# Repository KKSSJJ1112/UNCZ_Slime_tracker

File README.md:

<h2 align="center">🚧 開発中 / 개발중 / Under Development 🚧</h2>

---

# UNCZ SlimeVR Tracker

[🇯🇵 日本語](#日本語) | [🇰🇷 한국어](#한국어) | [🇺🇸 English](#english)

<p align="center">
  <!-- 実演GIF / 실연 GIF / Demo GIF -->
  
</p>

---

## 日本語

### 1. 概要

UNCZ SlimeVR Tracker は SlimeVR エコシステム互換のカスタム IMU トラッカーボードである。ESP32-C3 を中心に IMU・磁気センサ・バッテリー充電・昇降圧 DC-DC を 1 枚に統合し、USB-C 1 ポートで充電とファームウェア書き込みを兼ねる構成となっている。

- ボードサイズ: **約 50mm × 35mm**
- 電源: 1 セル Li-ion / Li-Po **1100mAh**
- 通信: Wi-Fi (ESP32-C3 内蔵)
- 充電/通信: USB-C 単一ポート
- 4 層 PCB 設計

### 2. 使用 IC 一覧

| 役割 | 型番 | 主な仕様 |
|------|------|----------|
| MCU | ESP32-C3-MINI-1-H4X | RISC-V, Wi-Fi/BLE, 内蔵アンテナ |
| 昇降圧 DC-DC | TPS63802DSGR | Iq 11µA, EN ピン制御 |
| 充電 IC | BQ24232HRGTR | パワーパス内蔵, OVP 28V |
| IMU | LSM6DSV16XTR | 6 軸, I²C 0x6B |
| 磁気センサ | QMC6309 | 3 軸, I²C 0x7C (オプション実装) |
| USB データ TVS | USBLC6-2SC6 | D+/D- ESD 保護 |
| バッテリー | 1100mAh 1S Li-ion/Li-Po | 公称 3.7V |

### 3. 出力 CLC フィルタ

TPS63802 の出力リップル抑制のため、共振周波数 **約 1.4MHz** をターゲットとした CLC フィルタを実装している。

**フィルタ構成**
- C1 (前段): **10µF**
- L: **1µH**
- C2 (後段): **10µF**
- 共振周波数: f₀ = 1 / (2π√(LC)) ≈ 1.59MHz (C 並列換算)

**スナバ・ダンピング**
LC 共振による Q 値スパイクを抑えるため、後段に並列スナバを配置。
- ダンピング抵抗: **1Ω 抵抗 × 3 個並列 = 0.33Ω**
- スナバ容量: **22µF × 3 個並列 = 66µF**

この構成によりフィルタの Q 値を適切に下げ、過渡応答時のリンギングを抑制している。

<p align="center">
  <!-- LTspice シミュレーション画像 -->
  
</p>

### 4. ファイル構成

| フォルダ | 内容 |
|----------|------|
| `pic/` | 測定写真、実演 GIF |
| `EASY_EDA_PRO/` | EasyEDA Pro プロジェクトファイル、ライブラリファイル |
| `JLC_PCB/` | ガーバーファイル、BOM、Pick & Place ファイル |
| `Datasheet/` | 使用部品のデータシート |
| `Firmware/` | SlimeVR オープンソースベースのファームウェア |
| `License/` | ライセンスファイル |

### 5. ファームウェア

本プロジェクトのファームウェアに関するすべての部分は **[SlimeVR オープンソースプロジェクト](https://github.com/SlimeVR/SlimeVR-Tracker-ESP)** に準拠する。

### 6. リビジョン履歴

| Rev | 内容 |
|-----|------|
| REV1 | モジュールベースの拡張ボード設計 |
| REV5 | チップベースの再設計 (現行) |

### 7. ライセンス

- **ハードウェア (PCB, 回路図, 3D ファイル)**: [MIT License](https://github.com/KKSSJJ1112/UNCZ_Slime_tracker/blob/main/License/MIT)
- **ドキュメント**: [CC BY-SA 4.0](https://creativecommons.org/licenses/by-sa/4.0/)

---

## 한국어

### 1. 개요

UNCZ SlimeVR Tracker는 SlimeVR 생태계와 호환되는 커스텀 IMU 트래커 보드입니다. ESP32-C3를 중심으로 IMU, 자력계, 배터리 충전 회로, 벅부스트 DC-DC를 한 장의 PCB에 통합했으며, 단일 USB-C 포트로 충전과 펌웨어 장입을 모두 처리합니다.

- 보드 사이즈: **약 50mm × 35mm**
- 전원: 1셀 Li-ion / Li-Po **1100mAh**
- 통신: Wi-Fi (ESP32-C3 내장)
- 충전/통신: USB-C 단일 포트
- 4레이어 PCB 설계

### 2. 사용 IC 목록

| 역할 | 부품 | 주요 사양 |
|------|------|-----------|
| MCU | ESP32-C3-MINI-1-H4X | RISC-V, Wi-Fi/BLE, 내장 안테나 |
| 벅부스트 DC-DC | TPS63802DSGR | Iq 11µA, EN 핀 제어 |
| 충전 IC | BQ24232HRGTR | 파워패스 내장, OVP 28V |
| IMU | LSM6DSV16XTR | 6축, I²C 0x6B |
| 자력계 | QMC6309 | 3축, I²C 0x7C (옵션 실장) |
| USB 데이터 TVS | USBLC6-2SC6 | D+/D- ESD 보호 |
| 배터리 | 1100mAh 1S Li-ion/Li-Po | 공칭 3.7V |

### 3. 출력 CLC 필터

TPS63802 출력 리플 억제를 위해 공진 주파수 **약 1.4MHz**를 타겟으로 한 CLC 필터를 구성했습니다.

**필터 구성**
- C1 (전단): **10µF**
- L: **1µH**
- C2 (후단): **10µF**
- 공진 주파수: f₀ = 1 / (2π√(LC)) ≈ 1.59MHz (C 병렬 환산)

**스너버 댐핑**
LC 공진으로 인한 Q값 스파이크를 억제하기 위해 후단에 병렬 스너버를 배치하여 의도적으로 Q값을 조정했습니다.
- 댐핑 저항: **1Ω 저항 3개 병렬 = 0.33Ω**
- 스너버 커패시터: **22µF 3개 병렬 = 66µF**

이 구성으로 필터의 Q값을 적절히 낮춰 과도 응답 시 링잉을 억제합니다.

<p align="center">
  <!-- LTspice 시뮬레이션 이미지 -->
  
</p>

### 4. 파일 구성

| 폴더 | 내용 |
|------|------|
| `pic/` | 측정 사진, 실연 GIF |
| `EASY_EDA_PRO/` | EasyEDA Pro 프로젝트 파일, 라이브러리 파일 |
| `JLC_PCB/` | 거버 파일, BOM, Pick & Place 파일 |
| `Datasheet/` | 사용 부품 데이터시트 |
| `Firmware/` | SlimeVR 오픈소스 기반 펌웨어 |
| `License/` | 라이센스 파일 |

### 5. 펌웨어

본 프로젝트의 펌웨어와 관련된 모든 부분은 **[SlimeVR 오픈소스 프로젝트](https://github.com/SlimeVR/SlimeVR-Tracker-ESP)** 를 따릅니다.

### 6. 리비전 히스토리

| Rev | 내용 |
|-----|------|
| REV1 | 모듈 기반의 확장 보드 설계 |
| REV5 | 칩 기반의 재설계 (현행) |

### 7. 라이센스

- **하드웨어 (PCB, 회로도, 3D 파일)**: [MIT License](https://github.com/KKSSJJ1112/UNCZ_Slime_tracker/blob/main/License/MIT)
- **문서**: [CC BY-SA 4.0](https://creativecommons.org/licenses/by-sa/4.0/)

---

## English

### 1. Overview

The UNCZ SlimeVR Tracker is a custom IMU tracker board compatible with the SlimeVR ecosystem. Built around the ESP32-C3, it integrates an IMU, magnetometer, battery charger, and buck-boost DC-DC converter onto a single PCB, with a single USB-C port handling both charging and firmware upload.

- Board size: **~50mm × 35mm**
- Power: 1-cell Li-ion / Li-Po **1100mAh**
- Communication: Wi-Fi (ESP32-C3 built-in)
- Charging/Communication: Single USB-C port
- 4-layer PCB design

### 2. IC List

| Role | Part | Key Specs |
|------|------|-----------|
| MCU | ESP32-C3-MINI-1-H4X | RISC-V, Wi-Fi/BLE, built-in antenna |
| Buck-Boost DC-DC | TPS63802DSGR | Iq 11µA, EN pin control |
| Charger IC | BQ24232HRGTR | Power path built-in, OVP 28V |
| IMU | LSM6DSV16XTR | 6-axis, I²C 0x6B |
| Magnetometer | QMC6309 | 3-axis, I²C 0x7C (optional) |
| USB Data TVS | USBLC6-2SC6 | D+/D- ESD protection |
| Battery | 1100mAh 1S Li-ion/Li-Po | Nominal 3.7V |

### 3. Output CLC Filter

A CLC filter targeting a resonant frequency of **~1.4MHz** is implemented to suppress output ripple from the TPS63802.

**Filter Configuration**
- C1 (front): **10µF**
- L: **1µH**
- C2 (rear): **10µF**
- Resonant frequency: f₀ = 1 / (2π√(LC)) ≈ 1.59MHz (with parallel C)

**Snubber Damping**
To suppress the Q-factor spike caused by LC resonance, a parallel snubber is placed at the rear stage, intentionally tuning the Q-factor.
- Damping resistor: **1Ω × 3 in parallel = 0.33Ω**
- Snubber capacitor: **22µF × 3 in parallel = 66µF**

This configuration appropriately lowers the filter's Q-factor, suppressing ringing during transient response.

<p align="center">
  <!-- LTspice simulation image -->
  
</p>

### 4. File Structure

| Folder | Contents |
|--------|----------|
| `pic/` | Measurement photos, demo GIFs |
| `EASY_EDA_PRO/` | EasyEDA Pro project files, library files |
| `JLC_PCB/` | Gerber files, BOM, Pick & Place files |
| `Datasheet/` | Datasheets of used components |
| `Firmware/` | SlimeVR open-source-based firmware |
| `License/` | License files |

### 5. Firmware

All firmware-related portions of this project follow the **[SlimeVR open-source project](https://github.com/SlimeVR/SlimeVR-Tracker-ESP)**.

### 6. Revision History

| Rev | Description |
|-----|-------------|
| REV1 | Module-based expansion board design |
| REV5 | Chip-based redesign (current) |

### 7. License

- **Hardware (PCB, Schematics, 3D files)**: [MIT License](https://github.com/KKSSJJ1112/UNCZ_Slime_tracker/blob/main/License/MIT)
- **Documentation**: [CC BY-SA 4.0](https://creativecommons.org/licenses/by-sa/4.0/)

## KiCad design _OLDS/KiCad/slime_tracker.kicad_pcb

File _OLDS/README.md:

# UNCZ_Slime_tracker

[English](#english) | [한국어](#한국어)

---

## English

### Overview
Custom SlimeVR tracker.

### Specifications
| Item | Description |
|------|-------------|
| MCU | ESP32-C3 Super Mini |
| IMU | SlimeVR Mumo Breakout Module V1 (ICM-45686 + QMC6309) |
| Battery | 1100mAh Li-Po |
| PCB Size | ~80mm x 30mm |

## REV01
<details>
### Features
- **Optimized Power Circuit**: Minimized ripple and noise (77mV → 20mV)
- **Compact Form Factor**: Streamlined 2-layer PCB design
- **Production Ready**: Includes JLCPCB manufacturing files

### Repository Structure
```
├── 3D/                    # 3D model files (STL - case, mount, etc.)
├── Datasheets/            # Component datasheets
├── Demonstration_Video/   # Demo videos
├── SlimeVR/               # SlimeVR firmware source code
├── KiCad/                 # KiCad project files
│   ├── *.kicad_pcb
│   ├── *.kicad_sch
│   └── *.kicad_pro
├── License/               # License files
├── Measurement_Pic/       # Power circuit ripple measurement photos
└── Production/            # Manufacturing files
    ├── BOM.csv            # Bill of Materials (JLCPCB format)
    └── Positions.csv      # Pick and place file
```

### Manufacturing
Production files are optimized for JLCPCB:
1. Generate Gerber and drill files from KiCad project (`KiCad/` folder)
2. Upload generated Gerber files to JLCPCB
3. Use provided BOM and position files for SMT assembly

### Firmware

Based on the official SlimeVR open-source firmware.  
Original repository: https://github.com/SlimeVR/SlimeVR-Tracker-ESP

This repository contains only the modified files. Clone the original repository first, then apply these changes.

#### Modified Files

| File | Changes |
|------|---------|
| `src/defines.h` | Hardcoded WiFi credentials, battery monitoring disabled, dual sensor config (`SENSOR_DESC_LIST` - 0x69, 0x68), SDO pin control (`PIN_IMU_SDO = 5`) |
| `src/main.cpp` | SDO pin initialization (GPIO5 → HIGH, 200ms delay), WiFi credentials fallback |
| `src/network/wifihandler.cpp` | Hardcoded WiFi credentials (`tryHardcodedCredentials()` function) |
| `src/network/wifihandler.h` | WiFi timeout reduced: 11s → 4s |
| `src/sensors/softfusion/drivers/icm45base.h` | Default I2C address changed: 0x68 → 0x69 |
| `board-defaults.json` | `BOARD_LOLIN_C3_MINI` dual sensor config (Sensor 0: 0x69, Sensor 1: 0x68) |
| `platformio.ini` | Upload flags adjusted (`--after=no_reset`) |

#### Key Features
- ✅ Dual sensor support (I2C address 0x68 + 0x69)
- ✅ Dynamic SDO pin control (GPIO5 for address separation)
- ✅ Improved WiFi stability (timeout adjustment, multiple fallback)
- ✅ Battery monitoring disabled

#### Dual Sensor Setup
When using 2 sensors, **short the INT pin of the secondary tracker to GND**.

#### Build & Flash
1. Install PlatformIO
2. Open `SlimeVR/` folder in VSCode
3. Build and upload to ESP32-C3

#### WiFi Configuration
Edit the following files and replace WiFi credentials:

1. **src/defines.h** (Line 13, 18)
   - Change `WIFI_CREDS_SSID` to your WiFi SSID
   - Change `WIFI_CREDS_PASSWD` to your WiFi password

2. **src/main.cpp** (Line 104, 105)
   - Change `WIFI_CREDS_SSID` to your WiFi SSID  
   - Change `WIFI_CREDS_PASSWD` to your WiFi password

3. **src/network/wifihandler.cpp** (Line 310, 311)
   - Change `HARDCODED_SSID` to your WiFi SSID
   - Change `HARDCODED_PASSWD` to your WiFi password

**Note:** All three locations must match for reliable WiFi connection.

### Power Circuit Measurement

77mV → 20mV  
From bottom to top: immediately after boost converter, after LC filter, and before final IMU power supply.
</details>

### License
- Hardware (PCB, Schematics, 3D files): [MIT License](License/MIT)
- Documentation: [CC BY-SA 4.0](https://creativecommons.org/licenses/by-sa/4.0/)

### Revision History
- **Rev03** (In Progress): Restructured power line routing and added TVS diode for ESD protection, added selectable resistor pads for I2C/SPI configuration, changed power control to EN/CE pin-based switching.
- **Rev02**: Power circuit, Charging circuit changed
- **Rev01**: Initial design

---

## 한국어

### 개요
커스텀 SlimeVR 트래커입니다.

### 사양
| 항목 | 내용 |
|------|------|
| MCU | ESP32-C3 Super Mini |
| IMU | SlimeVR Mumo Breakout Module V1 (ICM-45686 + QMC6309) |
| 배터리 | 1100mAh Li-Po |
| PCB 크기 | 약 80mm x 30mm |

## REV01
<details>
### 특징
- **전원부 최적화**: 리플 및 노이즈 최소화 (77mV → 20mV)
- **컴팩트 설계**: 2레이어 PCB 기반 간결한 설계
- **양산 대응**: JLCPCB 제조 파일 포함

### 저장소 구조
```
├── 3D/                    # 3D 모델 파일 (STL - 케이스, 마운트 등)
├── Datasheets/            # 부품 데이터시트
├── Demonstration_Video/   # 시연 영상
├── SlimeVR/               # SlimeVR 펌웨어 소스 코드
├── KiCad/                 # KiCad 프로젝트 파일
│   ├── *.kicad_pcb
│   ├── *.kicad_sch
│   └── *.kicad_pro
├── License/               # 라이선스 파일
├── Measurement_Pic/       # 전원부 리플 측정 사진
└── Production/            # 제조용 파일
    ├── BOM.csv            # 부품 목록 (JLCPCB 형식)
    └── Positions.csv      # 부품 배치 파일
```

### 제조 방법
JLCPCB 기준 제조 파일 제공:
1. KiCad 프로젝트(`KiCad/` 폴더)에서 Gerber 및 드릴 파일 생성
2. 생성된 Gerber 파일을 JLCPCB에 업로드
3. 제공된 BOM 및 위치 파일로 SMT 조립 주문

### 펌웨어

SlimeVR 공식 오픈소스 펌웨어를 기반으로 합니다.  
원본 저장소: https://github.com/SlimeVR/SlimeVR-Tracker-ESP

이 저장소에는 수정된 파일만 포함되어 있습니다. 원본 저장소를 먼저 클론한 후 변경사항을 적용하세요.

#### 수정된 파일

| 파일 | 변경 내용 |
|------|----------|
| `src/defines.h` | WiFi 정보 하드코딩, 배터리 모니터링 비활성화, 듀얼 센서 설정 (`SENSOR_DESC_LIST` - 0x69, 0x68), SDO 핀 제어 (`PIN_IMU_SDO = 5`) |
| `src/main.cpp` | SDO 핀 초기화 (GPIO5 → HIGH, 200ms delay), WiFi credentials fallback |
| `src/network/wifihandler.cpp` | WiFi 정보 하드코딩 (`tryHardcodedCredentials()` 함수) |
| `src/network/wifihandler.h` | WiFi 타임아웃 단축: 11초 → 4초 |
| `src/sensors/softfusion/drivers/icm45base.h` | I2C 기본 주소 변경: 0x68 → 0x69 |
| `board-defaults.json` | `BOARD_LOLIN_C3_MINI` 듀얼 센서 설정 (Sensor 0: 0x69, Sensor 1: 0x68) |
| `platformio.ini` | 업로드 플래그 조정 (`--after=no_reset`) |

#### 핵심 기능
- ✅ 듀얼 센서 지원 (I2C 주소 0x68 + 0x69)
- ✅ SDO 핀 동적 제어 (GPIO5로 센서 주소 분리)
- ✅ WiFi 안정성 개선 (타임아웃 조정, 다중 fallback)
- ✅ 배터리 모니터링 비활성화

#### 듀얼 센서 사용 시
센서 2개 사용 시, **보조 트래커의 INT 핀을 GND에 쇼트**시켜 사용하세요.

#### 빌드 및 업로드
1. PlatformIO 설치
2. VSCode에서 `SlimeVR/` 폴더 열기
3. ESP32-C3에 빌드 및 업로드

#### WiFi 설정
아래 파일들에서 WiFi 정보를 수정하세요:

1. **src/defines.h** (13, 18번째 줄)
   - `WIFI_CREDS_SSID`를 본인의 WiFi SSID로 변경
   - `WIFI_CREDS_PASSWD`를 본인의 WiFi 비밀번호로 변경

2. **src/main.cpp** (104, 105번째 줄)
   - `WIFI_CREDS_SSID`를 본인의 WiFi SSID로 변경
   - `WIFI_CREDS_PASSWD`를 본인의 WiFi 비밀번호로 변경

3. **src/network/wifihandler.cpp** (310, 311번째 줄)
   - `HARDCODED_SSID`를 본인의 WiFi SSID로 변경
   - `HARDCODED_PASSWD`를 본인의 WiFi 비밀번호로 변경

**참고:** 세 곳 모두 동일하게 설정해야 WiFi 연결이 정상 작동합니다.

### 전원부 측정

77mV → 20mV  
맨 아래부터 승압 직후, LC필터 이후, 최종 IMU 공급 직전
</details>
### 라이선스
- Hardware (PCB, Schematics, 3D files): [MIT License](License/MIT)
- Documentation: [CC BY-SA 4.0](https://creativecommons.org/licenses/by-sa/4.0/)

### 변경 이력
- **Rev03** (현재 진행중) : ESD관련한 배선 구조 변경 및 소자 추가, I2C, SPI 혼용을 위한 선택용 저항 패턴 추가, 전원제어를 EN, CE핀 기반으로 변경
- **Rev02**: 전원부, 충전부 수정
- **Rev01**: 최초 설계

---

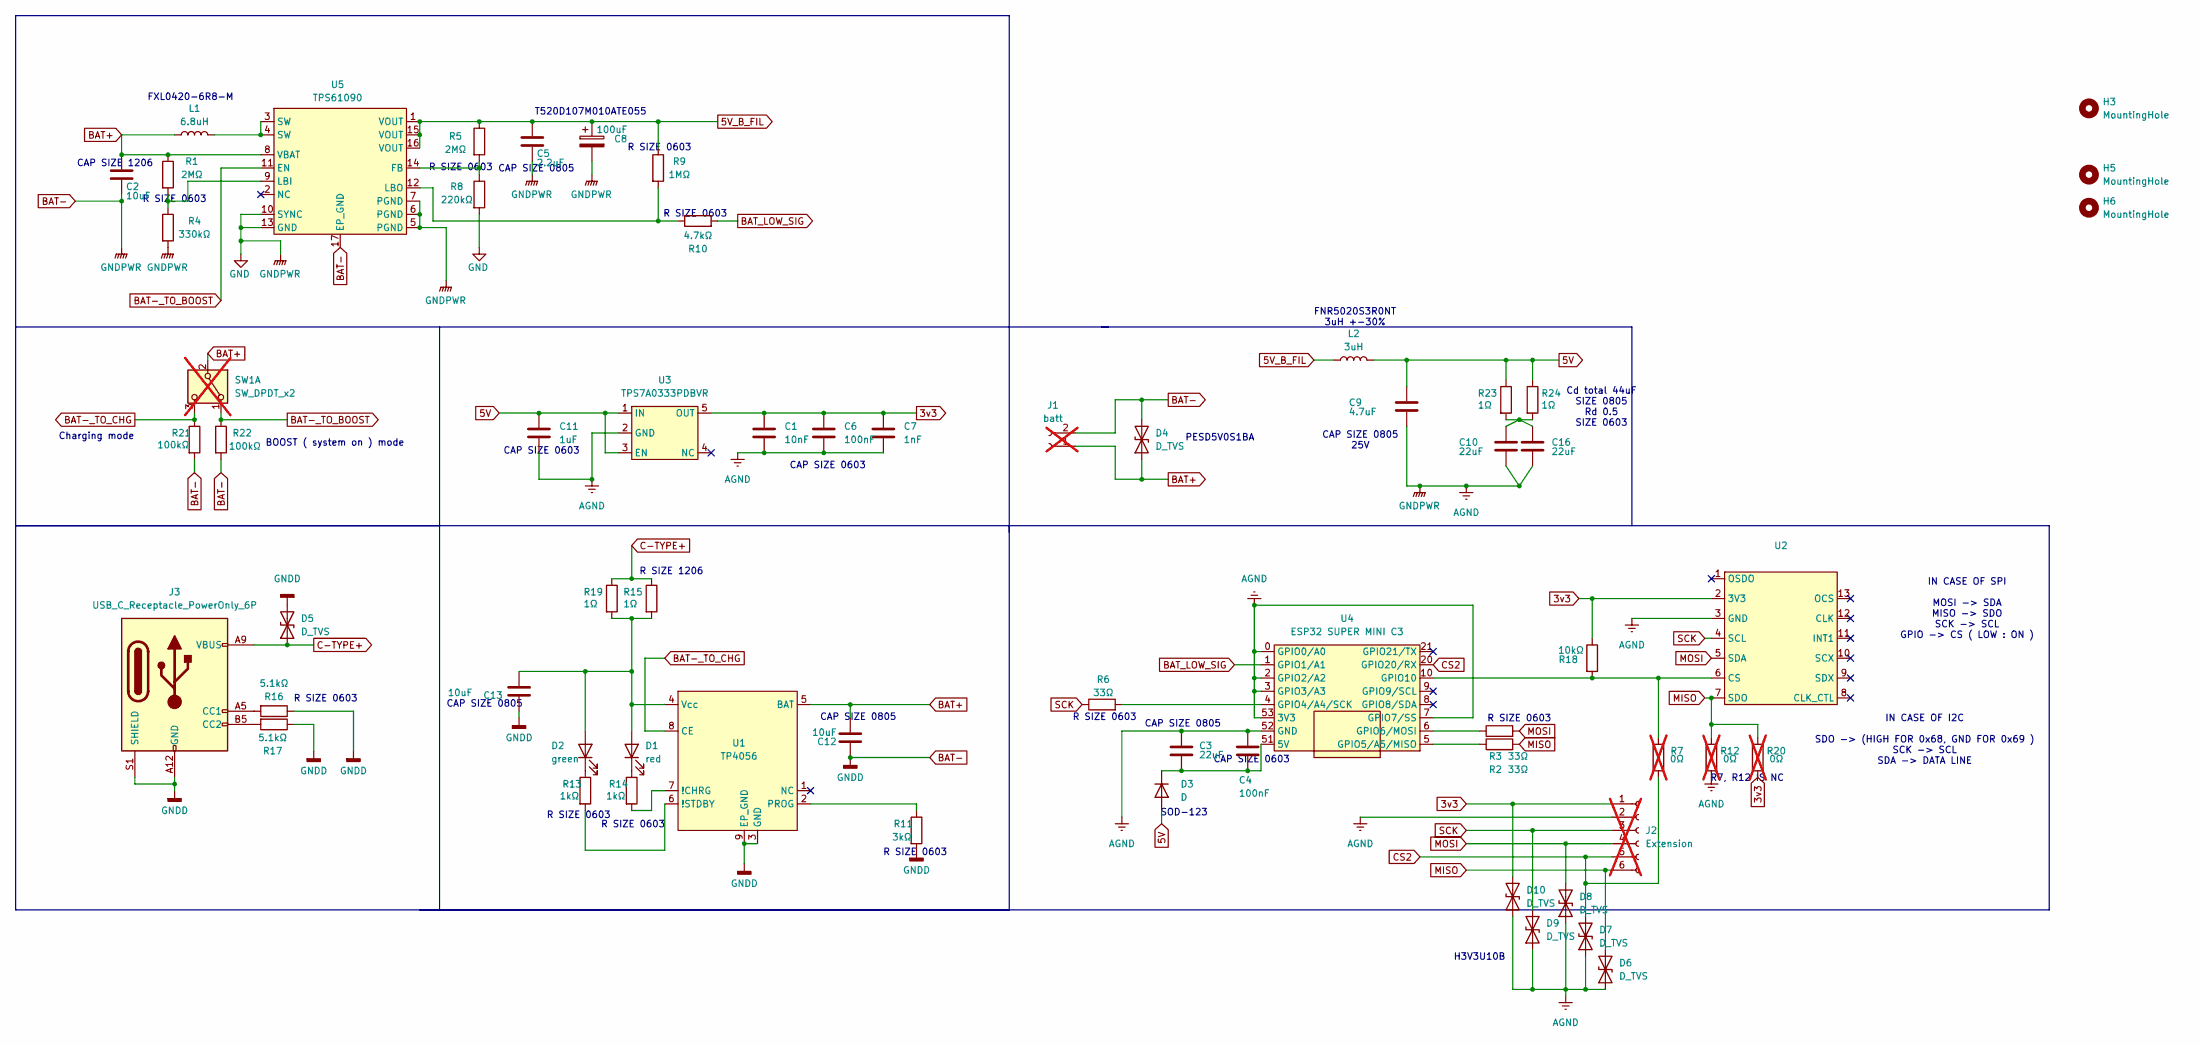
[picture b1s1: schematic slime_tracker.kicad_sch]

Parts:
C1: 10nF; C_0805_2012Metric
C2: 10uF; C_1206_3216Metric
C3, C10, C16: 22uF; C_0805_2012Metric
C4, C6: 100nF; C_0603_1608Metric
C5: 2.2uF; C_0805_2012Metric
C7: 1nF; C_0603_1608Metric
C8: 100uF; CP_EIA-7343-31_Kemet-D
C9: 4.7uF; C_0805_2012Metric
C11: 1uF; C_0603_1608Metric
C12, C13: 10uF; C_0805_2012Metric
D1: red; LED_0805_2012Metric
D2: green; LED_0805_2012Metric
D3: D; D_SOD-123
D4, D5: D_TVS; D_SOD-323
D6, D7, D8, D9, D10: D_TVS; DFN1006-2
H3, H5, H6: MountingHole; ToolingHole_1.152mm
J1: batt; JST_PH_S2B-PH-K_1x02_P2.00mm_Horizontal; not fitted
J2: Extension; JST_PH_S6B-PH-K_1x06_P2.00mm_Horizontal; not fitted
J3: USB_C_Receptacle_PowerOnly_6P; USB_C_Receptacle_GCT_USB4135-GF-A_6P_TopMnt_Horizontal
L1: 6.8uH; FXL0420
L2: 3uH; FNR5020S3R0NT
R1, R5: 2MΩ; R_0603_1608Metric
R2, R3, R6: 33Ω; R_0603_1608Metric
R4: 330kΩ; R_0603_1608Metric
R7, R12, R20: 0Ω; R_0603_1608Metric; not fitted
R8: 220kΩ; R_0603_1608Metric
R9: 1MΩ; R_0603_1608Metric
R10: 4.7kΩ; R_0603_1608Metric
R11: 3kΩ; R_0603_1608Metric
R13, R14: 1kΩ; R_0603_1608Metric
R15, R19: 1Ω; R_1206_3216Metric
R16, R17: 5.1kΩ; R_0603_1608Metric
R18: 10kΩ; R_0603_1608Metric
R21, R22: 100kΩ; R_0603_1608Metric
R23, R24: 1Ω; R_0603_1608Metric
SW1: SW_DPDT_x2; SW_Slide_SPDT_Angled_CK_OS102011MA1Q; not fitted
U1: TP4056; TP4056_ESOP8
U2: Slime_IMU_mumo
U3: TPS7A0333PDBVR; SOT-23-5
U4: ESP32 SUPER MINI C3; esp32
U5: TPS61090; QFN-16-1EP_4x4mm_P0.65mm_EP2.7x2.7mm_PullBack_ThermalVias

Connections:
3v3: C1.1, C6.1, C7.1, D10.2 (A2), J2.1, R18.1, R20.1, U2.2 (3V3), U3.5 (OUT)
5V: C9.2, C11.1, D3.2 (A), L2.2, R23.1, R24.1, U3.1 (IN), U3.3 (EN)
5V_B_FIL: C5.2, C8.1, L2.1, R5.1, R9.1, U5.1 (VOUT), U5.15 (VOUT), U5.16 (VOUT)
BAT+: C2.2, C12.1, D4.1 (A1), J1.1, L1.1, R1.1, SW1.2 (B), U1.5 (BAT), U5.8 (VBAT)
BAT-: C1.2, C2.1, C3.2, C4.2, C5.1, C6.2, C7.2, C8.2, C9.1, C10.1, C11.2, C12.2, C13.2, C16.1, D4.2 (A2), D5.2 (A2), D6.1 (A1), D7.1 (A1), D8.1 (A1), D9.1 (A1), D10.1 (A1), J1.2, J2.2, J3.A12 (GND), J3.B12 (GND), J3.S1 (SHIELD), R4.2, R8.2, R11.2, R12.1, R16.1, R17.1, R21.2, R22.2, U1.3 (GND), U1.9 (EP_GND), U2.3 (GND), U3.2 (GND), U4.0 (GPIO0/A0), U4.2 (GPIO2/A2), U4.3 (GPIO3/A3), U4.7 (GPIO7/SS), U4.52 (GND), U4.53 (3V3), U5.5 (PGND), U5.6 (PGND), U5.7 (PGND), U5.10 (SYNC), U5.13 (GND), U5.17 (EP_GND)
BAT-_TO_BOOST: R22.1, SW1.1 (A), U5.11 (EN)
BAT-_TO_CHG: R21.1, SW1.3 (C), U1.8 (CE)
BAT_LOW_SIG: R10.2, U4.1 (GPIO1/A1)
C-TYPE+: D5.1 (A1), J3.A9 (VBUS), J3.B9 (VBUS), R15.1, R19.1
CS2: D7.2 (A2), J2.5, R7.1, U4.20 (GPIO20/RX)
MISO: D6.2 (A2), J2.6, R2.2, R12.2, R20.2, U2.7 (SDO)
MOSI: D8.2 (A2), J2.4, R3.2, U2.5 (SDA)
unnamed: C10.2, C16.2, R23.2, R24.2
unnamed: C13.1, D1.2 (A), D2.2 (A), R15.2, R19.2, U1.4 (Vcc)
unnamed: D1.1 (K), R14.1
unnamed: D2.1 (K), R13.1
unnamed: C3.1, C4.1, D3.1 (K), U4.51 (5V)
unnamed: J3.A5 (CC1), R16.2
unnamed: J3.B5 (CC2), R17.2
unnamed: L1.2, U5.3 (SW), U5.4 (SW)
unnamed: R14.2, U1.7 (!CHRG)
unnamed: R13.2, U1.6 (!STDBY)
unnamed: R11.1, U1.2 (PROG)
unnamed: R7.2, R18.2, U2.6 (CS), U4.10 (GPIO10)
unnamed: R6.2, U4.4 (GPIO4/A4/SCK)
unnamed: R2.1, U4.5 (GPIO5/A5/MISO)
unnamed: R3.1, U4.6 (GPIO6/MOSI)
unnamed: R5.2, R8.1, U5.14 (FB)
unnamed: R1.2, R4.1, U5.9 (LBI)
unnamed: R9.2, R10.1, U5.12 (LBO)
SCK: D9.2 (A2), J2.3, R6.1, U2.4 (SCL)

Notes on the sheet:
H3V3U10B
CAP SIZE 0603
R SIZE 0603
CAP SIZE 0603
R SIZE 1206
BOOST ( system on ) mode
CAP SIZE 0805
Cd total 44uF SIZE 0805 Rd 0.5 SIZE 0603
FNR5020S3R0NT 3uH +-30%
CAP SIZE 0805 25V
IN CASE OF I2C SDO -> (HIGH FOR 0x68, GND FOR 0x69 ) SCK -> SCL SDA -> DATA LINE
T520D107M010ATE055
FXL0420-6R8-M
SOD-123
Charging mode
PESD5V0S1BA
CAP SIZE 1206
R7, R12 IS NC
IN CASE OF SPI MOSI -> SDA MISO -> SDO SCK -> SCL GPIO -> CS ( LOW : ON )

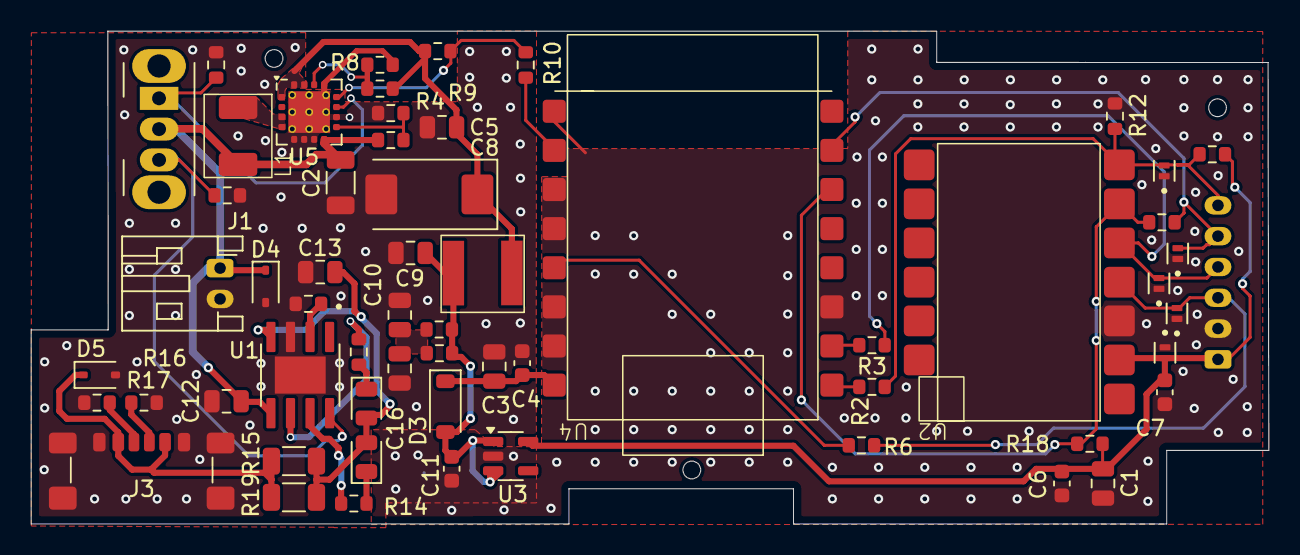
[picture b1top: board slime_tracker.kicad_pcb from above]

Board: 2 copper layers, 80.4 x 32.0 mm, 62 parts (0 on the bottom side), 31 nets.

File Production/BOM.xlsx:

Value | Reference | Qty | Footprint | JLCPCB Part #
1uF | C1 | 1 | Capacitor_SMD:C_0805_2012Metric | C28323
10uF | C2,C12,C13 | 3 | Capacitor_SMD:C_1206_3216Metric | C13585
22uF | C3 | 1 | Capacitor_SMD:C_1206_3216Metric | C12891
100nF | C4 | 1 | Capacitor_SMD:C_1206_3216Metric | C24497
2.2uF | C5 | 1 | Capacitor_SMD:C_1206_3216Metric | C50254
10uF | C6 | 1 | Capacitor_SMD:C_0805_2012Metric | C15850
100nF | C7 | 1 | Capacitor_SMD:C_0805_2012Metric | C49678
100uF | C8 | 1 | CASE-V-7343-19 | C219004
4.7uF | C10 | 1 | Capacitor_SMD:C_1206_3216Metric | C29823
1uF | C11 | 1 | Capacitor_SMD:C_1206_3216Metric | C1848
red | D1 | 1 | LED_SMD:LED_0805_2012Metric | C84256
green | D2 | 1 | LED_SMD:LED_0805_2012Metric | C2297
D | D3 | 1 | Diode_SMD:D_SOD-123 | C7420328
FerriteBead | FB1 | 1 | Resistor_SMD:R_0805_2012Metric | C1017
USB_C_Receptacle_PowerOnly_6P | J3 | 1 | Connector_USB:USB_C_Receptacle_GCT_USB4135-GF-A_6P_TopMnt_Horizontal | C5438410
6.8uH | L1 | 1 | slime:FXL0420 | C177241
2.2uH | L2 | 1 | slime:FXL0420 | C167206
2MΩ | R1,R5 | 2 | Resistor_SMD:R_0603_1608Metric | C22976
33Ω | R2,R3,R6 | 3 | Resistor_SMD:R_0603_1608Metric | C23140
330kΩ | R4 | 1 | Resistor_SMD:R_0603_1608Metric | C23137
220kΩ | R8 | 1 | Resistor_SMD:R_0603_1608Metric | C22961
1MΩ | R9 | 1 | Resistor_SMD:R_0603_1608Metric | C22935
4.7kΩ | R10 | 1 | Resistor_SMD:R_0603_1608Metric | C23162
2kΩ | R11 | 1 | Resistor_SMD:R_0603_1608Metric | C22975
10kΩ | R18 | 2 | Resistor_SMD:R_0603_1608Metric | C25804
1kΩ | R13,R14 | 2 | Resistor_SMD:R_0603_1608Metric | C21190
1Ω | R15,R19 | 2 | Resistor_SMD:R_1206_3216Metric | C17928
5.1kΩ | R16,R17 | 2 | Resistor_SMD:R_0603_1608Metric | C23186
TP4056 | U1 | 1 | slime:TP4056_ESOP8 | C725790
TPS7A0333PDBVR | U3 | 1 | Package_TO_SOT_SMD:SOT-23-5 | C3749797
TPS61090 | U5 | 1 | Package_DFN_QFN:QFN-16-1EP_4x4mm_P0.65mm_EP2.7x2.7mm_PullBack_ThermalVias | C206167

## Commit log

2025-11-12 Add files via upload
    schematics for Slime tracker.
2025-11-13 아트워크 진행중
2025-11-17 ground plane
2025-11-17 art-work-almost-done
2025-11-18 bom. jlc pcb part confirmed
2025-11-18 type-c
2025-11-19 parts changed
2025-11-23 1123
2025-11-25 11_25_SPI_DONE
2025-12-16 Rename top final.stl to 3D/top final.stl
2025-12-16 Create .t.
2025-12-16 kicad project
2025-12-16 Rev_02
2025-12-16 readme
2025-12-16 for JLC
2025-12-16 Simplify overview and features descriptions
    Removed redundant phrases in the overview and features sections for clarity.
2025-12-31 Rename 1--00223.jpg to ripple_comparison.jpg
2025-12-31 Measurement
2026-01-16 new dcdc converter
    only tantalum cap 100uf -> 220uf and R will be change. not yet.
2026-03-05 REV0.3
    REV 0.3
    TVS, EN/CE Based control, SPI I2C selectable Footprint, ESP32 Footprint changed, etc
2026-03-05 REV 0.3
    REV 0.3
    TVS, EN/CE Based control, SPI I2C selectable Footprint, ESP32 Footprint changed, etc
2026-03-05 REV03
    In Progress
2026-03-06 REV3 TD
    TeadDrop
2026-03-09 REV_03
    LC filter damp R added
    USB Vbus TVS added
2026-03-10 Rev 03 more TVS
    more TVS at extend port line
2026-03-11 REV03 3/11
    few PCB layout changed
2026-03-12 rev03 agnd pgnd
    agnd pgnd
2026-03-19 LPF Changed
    dd
2026-03-19 배치 안함
    추가
2026-03-19 REV03
2026-03-19 Create hehe
2026-03-19 REV03 BOM
2026-03-20 bom com
    bom com
2026-03-20 rev03 almost
    com
2026-03-20 layout edge cut
2026-03-20 pos file
2026-03-20 board cut
    cc
2026-05-23 REV05_DEV
2026-05-23 datasheets
2026-05-23 REV05_MD_START
2026-05-23 EASY_EDA
2026-05-26 scale
2026-05-26 SMAW-250
